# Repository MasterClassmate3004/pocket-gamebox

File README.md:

<h2>Pocket Gamebox</h2>

A handheld gaming device that fits right into your pocket. For more professional experience, also includes a custom gamebox holder. 

The first version of the code includes two different games (the brick and the snake game) and a home screen to select one of them. More games to hopefully follow in the future.

The pocket game box uses a 2.4inch LCD, 240x320. For it's microprocessor, it uses a Raspberry Pi Pico. It has 6 switches to control the gaming console. 
Additionally for CAD, a bottom and top case were designed, while a gamebox holder was also later designed which I didn't think of earlier.

I created this after seeing the Wrong Hack Club challenge and decided to design my own handheld gaming device. I really enjoy gaming and think this could be a good addition to my gaming closet. 

<br><br><br>

<h3>Final Assembly</h3>
<hr>
This is the final assembly of the project with the holder, cases and the PCB.

<br><br>

<h3>Schematics</h3>
<hr>
This is the schematics I designed for the pcb on kicad, it includes 6 keys, the lcd display and the arduino pico.

<br><br>

<h3>PCB</h3>
<hr>
This is the pcb design after routing all components as connected in the schematics. It's kinda tiring but fulfilling.

<br><br>

<h3>Bottom Case</h3>
<hr>
This is the bottom case in which the actual pcb would be placed. Hopefully i got all the dimensions right!
After soldering your components onto your PCB, place them below the display stage. Screw the display on the display stage then. Make connections from the pcb to the display using jumper wires. <br>

<br><br>

<h3>Top Case</h3>
<hr>
This is the top case to cover the pcb and close the handheld gaming device, with also an opening for the usb-c port and the lcd display.

Fit the top case on the bottom case ensuring the keys come out properly of the respective gaps. Fix it firmly.

<br><br>

<h3>Holder</h3>
<hr>

<br><br>

<h3>Firmware</h3>
<hr>
After this, upload the code on the Arduino Pico using the firmware files and the Arduino IDE. After connecting the Pico with your computer using a cable, select the port and board on the IDE and upload the code. Everytime you want to play next, just connect the pico to a power supply with the code running and keep playing the games for days!

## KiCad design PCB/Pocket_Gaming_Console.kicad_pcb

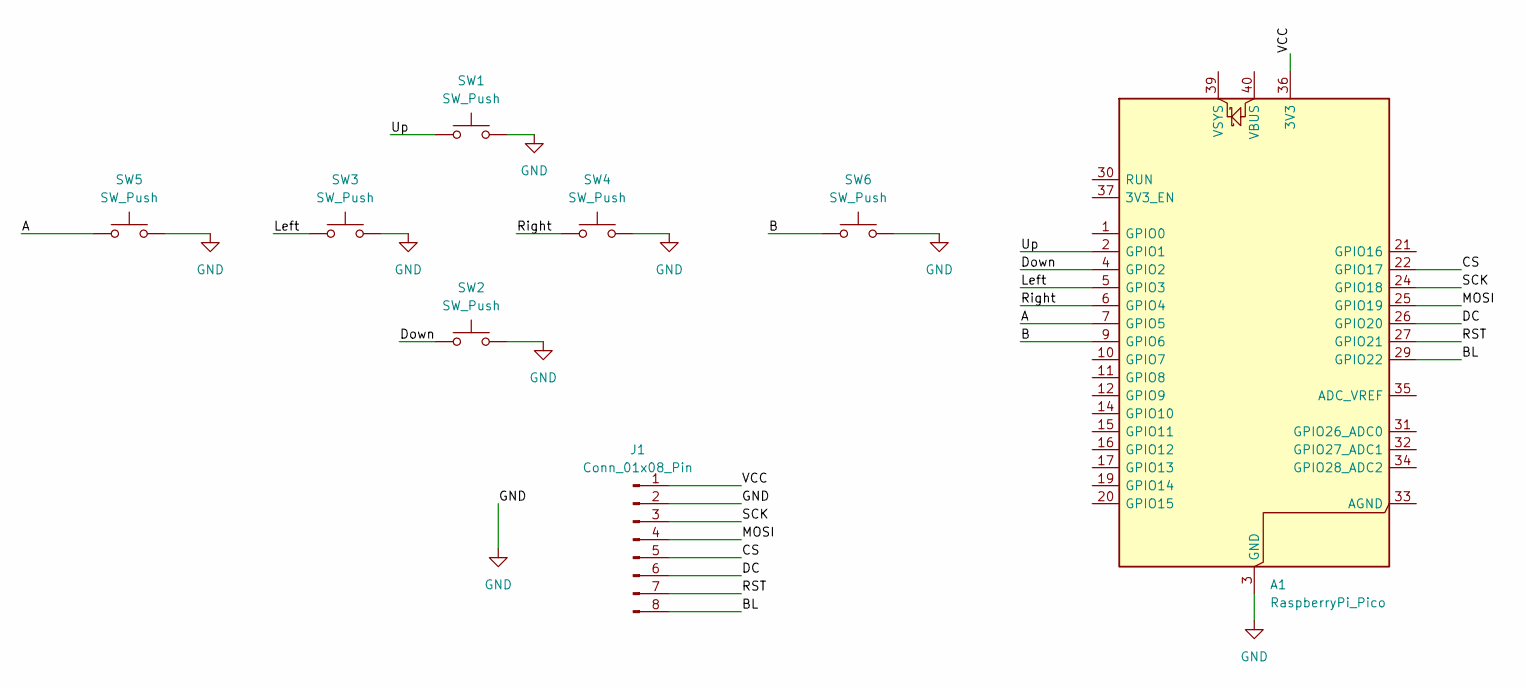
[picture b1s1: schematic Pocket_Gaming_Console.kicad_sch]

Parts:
A1: RaspberryPi_Pico; RaspberryPi_Pico_Common_Unspecified
J1: Conn_01x08_Pin; PinSocket_1x08_P2.54mm_Vertical
SW1, SW2, SW3, SW4, SW5, SW6: SW_Push; SW_Cherry_MX_1.00u_PCB

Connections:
/A: A1.7 (GPIO5), SW5.1
/B: A1.9 (GPIO6), SW6.1
/BL: A1.29 (GPIO22), J1.8
/CS: A1.22 (GPIO17), J1.5
/DC: A1.26 (GPIO20), J1.6
/Down: A1.4 (GPIO2), SW2.1
/Left: A1.5 (GPIO3), SW3.1
/MOSI: A1.25 (GPIO19), J1.4
/RST: A1.27 (GPIO21), J1.7
/Right: A1.6 (GPIO4), SW4.1
/SCK: A1.24 (GPIO18), J1.3
/Up: A1.2 (GPIO1), SW1.1
/VCC: A1.36 (3V3), J1.1
GND: A1.3 (GND), A1.8 (GND), A1.13 (GND), A1.18 (GND), A1.23 (GND), A1.28 (GND), A1.38 (GND), J1.2, SW1.2, SW2.2, SW3.2, SW4.2, SW5.2, SW6.2

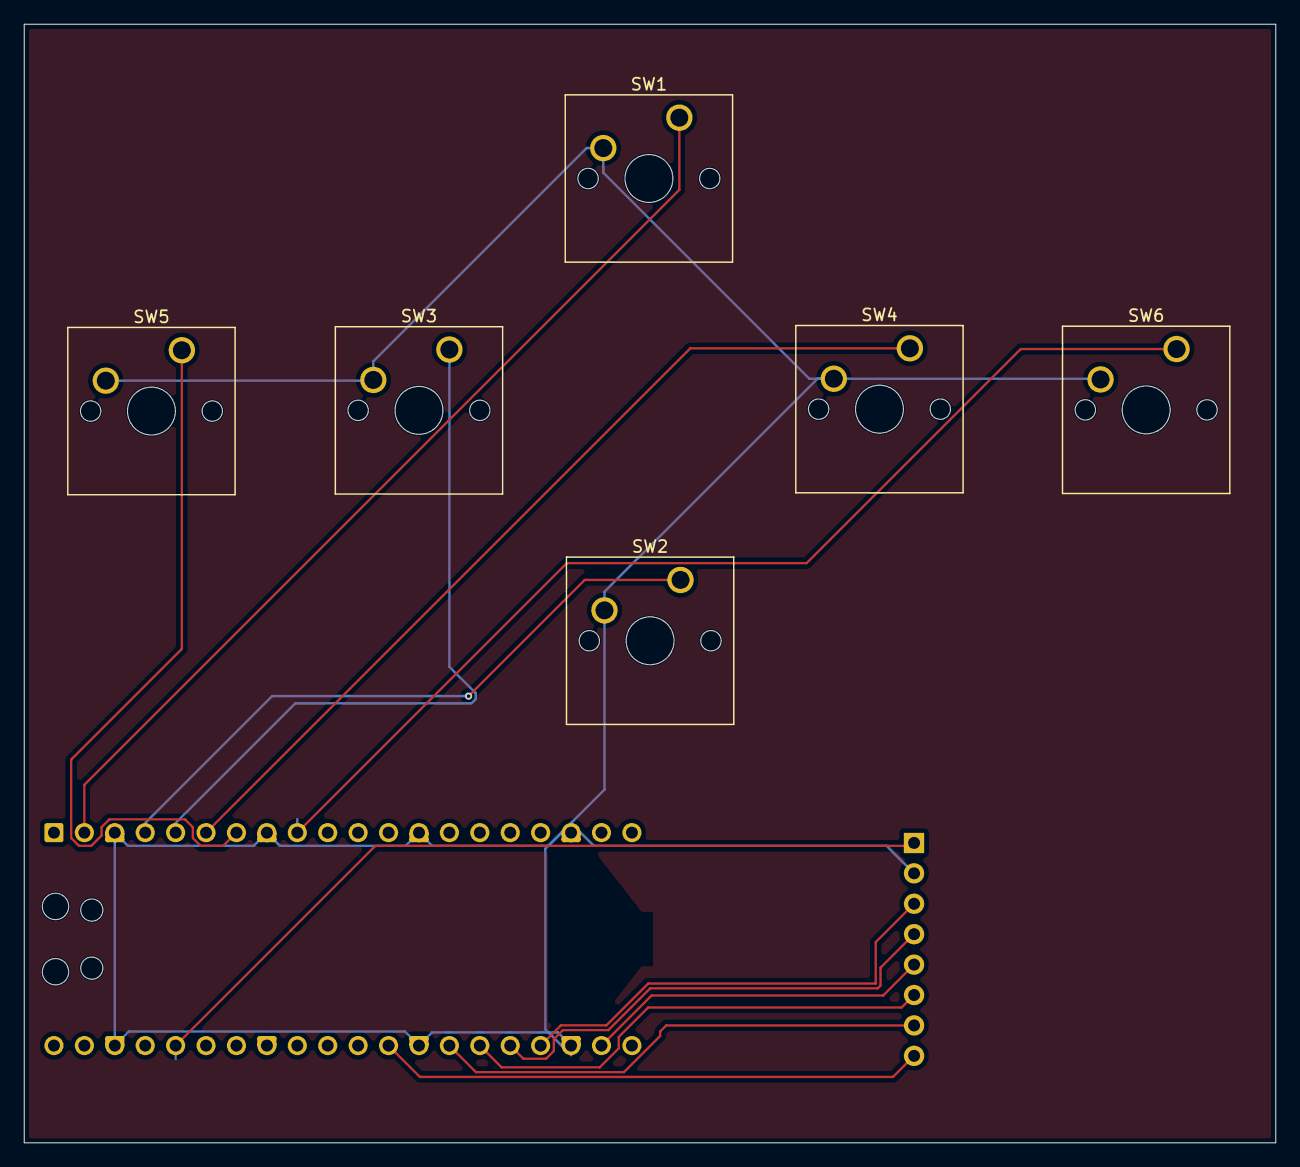
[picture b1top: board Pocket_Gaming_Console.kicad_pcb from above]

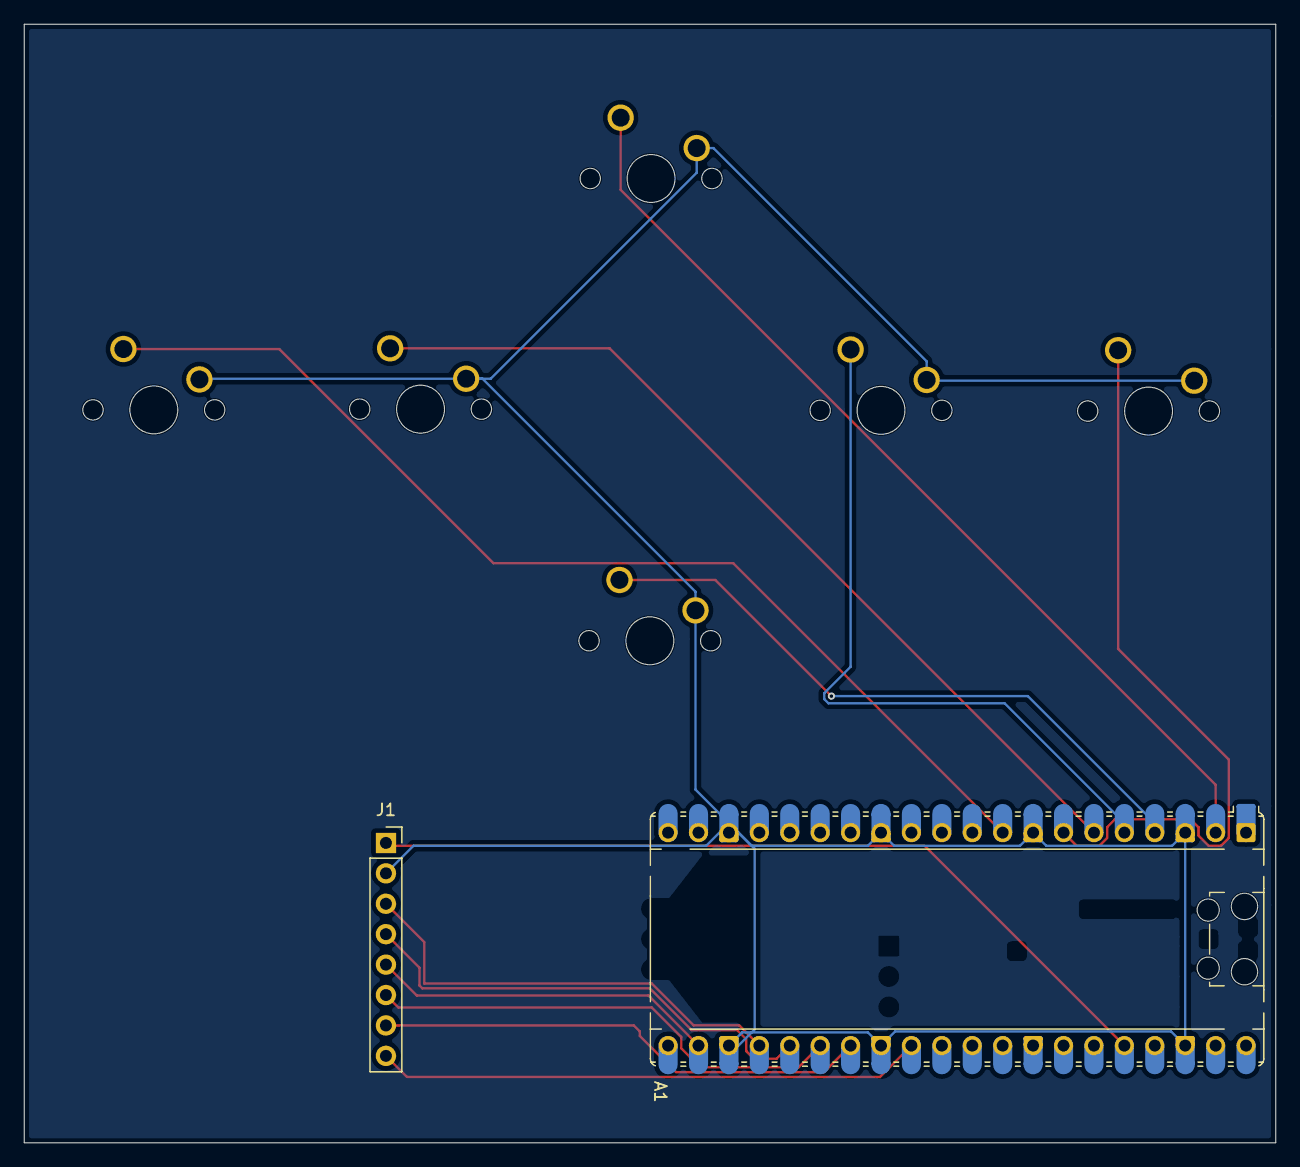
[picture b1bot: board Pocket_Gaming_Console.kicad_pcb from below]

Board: 2 copper layers, 104.5 x 93.4 mm, 8 parts (2 on the bottom side), 14 nets.
